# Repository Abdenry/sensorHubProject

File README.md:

# Sensor Hub

A small, portable, self-sustaining weather station built to provide data to an external web interface hosted with Grafana via a Raspberry Pi Zero 2 W. This station is able to collect various metrics from on board sensors such as temperature, humidity, heat index, wind speed, and wind direction. A **DHT22** sensor is used to collect relative humidity and temperature metrics with an accuracy of +-2% and +-0.5C, while metrics such as wind speed and wind direction are collected with custom built sensors. The heat index is calculated in software using the [DHT-sensor-library](https://github.com/adafruit/DHT-sensor-library).

Communication is handled through the NRF24l01 radio modules in a mesh configuration. The mesh routing of data packets is automatically managed with `RF24.h`, `RF24Network.h`, and `RF24Mesh.h` provided by the [RF24](https://github.com/nRF24/RF24?tab=readme-ov-file) library, specifically chosen for its meshing capabilities. It provides dynamic configuration of the NRF24l01 modules, meaning that in the scenario where the weather station loses connection with the Raspberry Pi for any reason (power down, range lost, etc.), it can automatically reconfigure and connect to the Raspberry Pi given its under normal operable condition (i.e. has power and is in range). This allows additional stations to be installed with potentially different purposes with all metrics collected to be routed back to the Raspberry Pi. Alternatively, if the distance between the Raspberry Pi and the weather station is much greater than the range of a single NRF24l01 module, an additional node can be configured and placed in between the weather station and Raspberry Pi acting as a range extender. The RF24 library will automatically handle the routing and pass the data collected from the weather station to the Raspberry Pi via that additional node. There is no limitation that prevents an additional station from also being a range extending node.

### Wiring Diagram

### CAD Model

## Sensor Design
The following sensor assemblies were all 3D printed out of white PET-G filament for its UV resistance, and to reflect as much heat as possible to avoid compromising the temperature and humidity readings of the DHT22 sensor.
### Solar Radiation Shield
The DHT22 sensor used to collect temperature and humidity data was housed in a solar radiation shield. This is necessary to prevent direct sunlight from heating the sensor over time creating higher than ambient temperature readings, simultaneously it protects the sensor from rainfall, which would also cause a higher than ambient humidity reading if it gets wet.

### Wind Vane
Wind direction was measured using eight AH180 omni-polar hall effect sensors and a magnet on the underside of the vane. Each hall effect sensor acts as one of the four cardinal or ordinal directions (North, North East, East, etc.) which is activated only in the presence of the magnet. The vane will point in the direction the wind is blowing **from**. With limited IO available on the Arduino Nano/ATmega328p the SN74HC175N Parallel In Serial Out (PISO) Shift Register was used to reduce the eight outputs of the wind vane to one output + three inputs, halving the total amount of connections to the Arduino Nano/ATmega328p.

### Anemometer
Wind speed was measured using two magnets and a single US1881 latching hall effect sensor connected to the Arduino Nano D2 pin which corresponds to the ATmega328p external interrupt pin 0 (PD2). The magnets attached to the underside of the anemometer rotate over the US1881 sensor triggering either a high or low state depending on the magnets polarity, generating an interrupt which increments a revolution counter. The `getWindSpeed()` function is called periodically to calculate the wind speed using the amount of revolutions counted within that period, resetting the revolution counter once calculation has completed, and repeats this process. This assembly was tested by having the anemometer attached externally to a moving car, logging its calculated wind speed and comparing it to that the vehicles actual speed. It proved accurate to +-2 km/h with a vehicle speed of 80 km/h.

## Grafana Dashboard
The Grafana dashboard conveniently displays historical readings for temperature, humidity, wind speed, and direction. It also provides an updated reading of the stations current temperature, humidity, and calculated heat index. The dashboard has been configured to retain this information for up to two weeks however this can be further increased if desired.

## Power Supply and Challenges Faced
Power for the station comes from a 1100 mAh LiPo battery, supported by four 1W solar panels connected in parallel. A solar power manager with Maximum Power Point Tracking (MPPT) is implemented to maximise the efficiency of the solar panels, switching between charging the station and its battery based on sunlight availability. It ensures that the battery remains charged during daylight hours, with enough capacity to keep the station operational overnight. After optimisations, the weather station consumes approximately 0.021 A at 3.72 V, providing an estimated 52 hours of operation without any solar input.

Prior to optimising power consumption, a major challenge faced during development was the intermittent loss of communications particularly over night.

Initially, it was suspected that the issue was not related to power due to the assumption that the 4 watt solar panel array was capable of powering and charging the station which had a measured active consumption of 0.24W (65mA @ 3.7V). After investigating the issue for a significant period of time, no definitive answer could explain the intermittent communication loss overnight other than insufficient solar power. To prove this was the root of the problem the station was connected to a bench top power supply with a constant 3.7V over night. This resulted in no communication drop outs over night nor for the next couple of days as the battery was sufficiently charged from the constant 3.7 V provided by the power supply. Optimisations for the code then proceeded to lower the active consumption.

### Optimisations
The first optimisation was replacing the software timer used to intermittently send weather metrics to the Raspberry Pi to a Watchdog Timer. This did not directly improve the power consumption of the station, however, it would allow the station to wake up from a power down mode, which was the second optimisation performed.

Entering the Arduino Nano/ATmega328p into a power down mode and only powering up after the Watchdog Timer expired directly reduced power consumption from 0.24W (65mA @ 3.7V) to 0.208W (56mA @ 3.7V), a 13% power efficiency improvement.

This was further improved by 64% by powering down the NRF24l01 radio module when not in use. This lowered the active consumption of the station to just 0.0744W (20mA @ 3.7V). This is a total 69% improvement from the initial 0.24W (65mA @ 3.7V) observed prior to optimising.

With the stations active power consumption optimised, the 4W solar panel array was able to sufficiently charge and power the station eliminating the intermittent communication loss.

## Future Improvements
- This station could be improved in the future with the inclusion of a rainfall sensor to collect metrics on the volume and rate of rainfall. One possible design for this sensor could involve a tipping bucket mechanism, where a known volume of rain causes a bucket to tip, triggering a hall-effect sensor to log the event. By counting the frequency of tipping, the system could accurately measure rate and cumulative rainfall over time.
- Improvements could also be made to the assembly of the custom sensors to be more accessible for servicing as the current design is finicky to put together, not suitable for consistently taking apart and putting back together.
- The internal wiring of the station could also be significantly improved by switching the single core wire used for **each** connection, to a multi-core cable. This could make the internal wiring much tidier and easier to access/service.

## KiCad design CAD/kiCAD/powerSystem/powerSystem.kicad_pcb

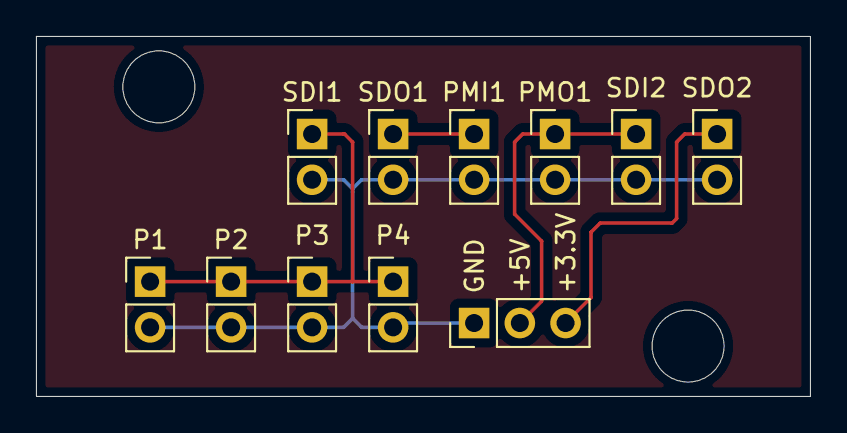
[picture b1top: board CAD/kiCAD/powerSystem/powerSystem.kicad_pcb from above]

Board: 2 copper layers, 43.0 x 20.0 mm, 11 parts (0 on the bottom side), 5 nets.

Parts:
P1, P2, P3, P4: Conn_01x02; PinHeader_1x02_P2.54mm_Vertical
PMI1: Conn_01x02; PinHeader_1x02_P2.54mm_Vertical
PMO1: Conn_01x02; PinHeader_1x02_P2.54mm_Vertical
SDI1, SDI2: Conn_01x02; PinHeader_1x02_P2.54mm_Vertical
SDO1, SDO2: Conn_01x02; PinHeader_1x02_P2.54mm_Vertical
SIGOUT1: Conn_01x03; PinHeader_1x03_P2.54mm_Vertical

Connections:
/0~10V: P1.1, P2.1, P3.1, P4.1, SDI1.1
/+3_3V: SDO2.1, SIGOUT1.3
/+5.5V: PMI1.1, SDO1.1
/+5V: PMO1.1, SDI2.1, SIGOUT1.2
/GND: P1.2, P2.2, P3.2, P4.2, PMI1.2, PMO1.2, SDI1.2, SDI2.2, SDO1.2, SDO2.2, SIGOUT1.1

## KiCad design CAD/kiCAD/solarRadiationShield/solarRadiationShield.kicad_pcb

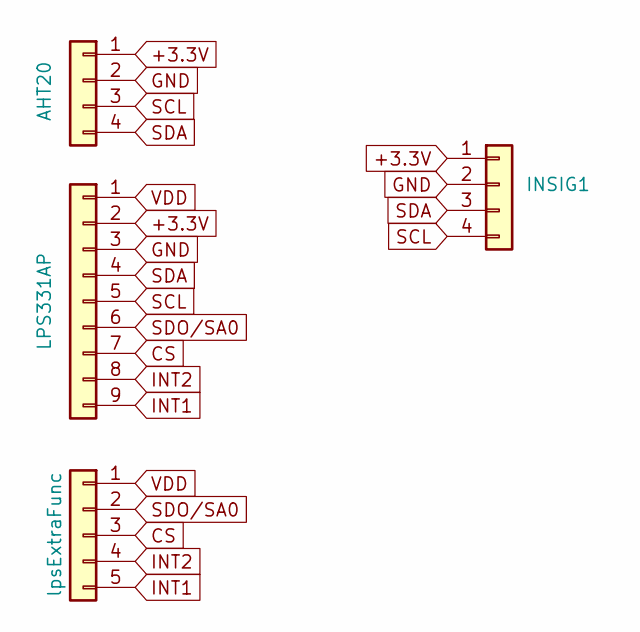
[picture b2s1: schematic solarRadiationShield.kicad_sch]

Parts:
AHT20: AHT20; PinHeader_1x04_P2.54mm_Vertical
INSIG1: INSIG; PinHeader_1x04_P2.54mm_Vertical
LPS331AP1: LPS331AP; PinHeader_1x09_P2.54mm_Vertical
lpsExtraFunc1: lpsExtraFunc; PinHeader_1x05_P2.54mm_Vertical

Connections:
+3.3V: AHT20.1, INSIG1.1, LPS331AP1.2
CS: LPS331AP1.7, lpsExtraFunc1.3
GND: AHT20.2, INSIG1.2, LPS331AP1.3
INT1: LPS331AP1.9, lpsExtraFunc1.5
INT2: LPS331AP1.8, lpsExtraFunc1.4
SCL: AHT20.3, INSIG1.4, LPS331AP1.5
SDA: AHT20.4, INSIG1.3, LPS331AP1.4
SDO/SA0: LPS331AP1.6, lpsExtraFunc1.2
VDD: LPS331AP1.1, lpsExtraFunc1.1

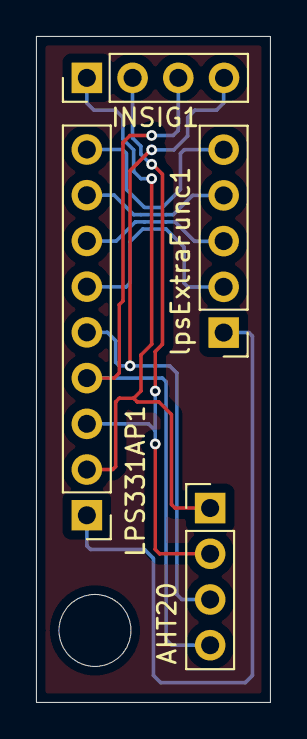
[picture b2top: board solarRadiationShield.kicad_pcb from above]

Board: 2 copper layers, 13.0 x 37.0 mm, 4 parts (0 on the bottom side), 9 nets.

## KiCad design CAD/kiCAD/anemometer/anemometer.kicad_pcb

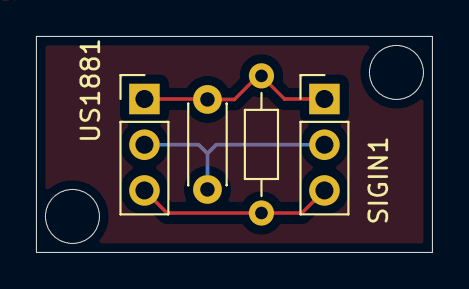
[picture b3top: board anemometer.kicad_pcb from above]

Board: 2 copper layers, 22.0 x 12.0 mm, 4 parts (0 on the bottom side), 3 nets.

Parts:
C1: 100nF; C_Disc_D4.3mm_W1.9mm_P5.00mm
R1: 10k; R_Axial_DIN0204_L3.6mm_D1.6mm_P7.62mm_Horizontal
SIGIN1: Conn_01x03; PinHeader_1x03_P2.54mm_Vertical
US1881: Conn_01x03; PinHeader_1x03_P2.54mm_Vertical

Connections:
GND: C1.1, SIGIN1.2, US1881.2
OUT: R1.2, SIGIN1.3, US1881.3
VDD: C1.2, R1.1, SIGIN1.1, US1881.1

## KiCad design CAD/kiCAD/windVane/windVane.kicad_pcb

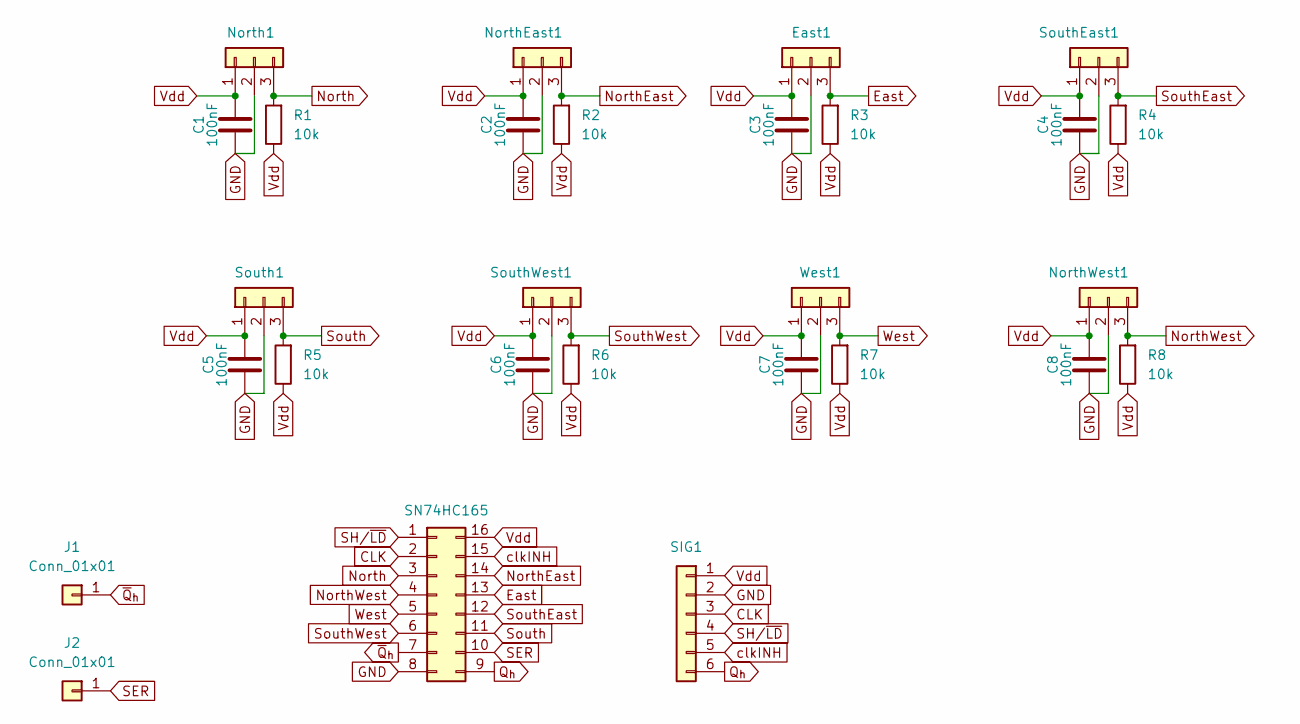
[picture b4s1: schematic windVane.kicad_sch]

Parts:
C1, C2, C3, C4, C5, C6, C7, C8: 100nF; C_0402_1005Metric
East1: Conn_01x03; PinHeader_1x03_P2.54mm_Vertical
J1, J2: Conn_01x01; PinHeader_1x01_P2.54mm_Vertical
North1: Conn_01x03; PinHeader_1x03_P2.54mm_Vertical
NorthEast1: Conn_01x03; PinHeader_1x03_P2.54mm_Vertical
NorthWest1: Conn_01x03; PinHeader_1x03_P2.54mm_Vertical
R1, R2, R3, R4, R5, R6, R7, R8: 10k; R_0402_1005Metric
SIG1: Conn_01x06; PinHeader_1x06_P2.54mm_Vertical
SN74HC165: Conn_02x08_Counter_Clockwise; DIP-16_W7.62mm
South1: Conn_01x03; PinHeader_1x03_P2.54mm_Vertical
SouthEast1: Conn_01x03; PinHeader_1x03_P2.54mm_Vertical
SouthWest1: Conn_01x03; PinHeader_1x03_P2.54mm_Vertical
West1: Conn_01x03; PinHeader_1x03_P2.54mm_Vertical

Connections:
CLK: SIG1.3, SN74HC165.2
East: East1.3, R3.2, SN74HC165.13
GND: C1.1, C2.1, C3.1, C4.1, C5.1, C6.1, C7.1, C8.1, East1.2, North1.2, NorthEast1.2, NorthWest1.2, SIG1.2, SN74HC165.8, South1.2, SouthEast1.2, SouthWest1.2, West1.2
North: North1.3, R1.2, SN74HC165.3
NorthEast: NorthEast1.3, R2.2, SN74HC165.14
NorthWest: NorthWest1.3, R8.2, SN74HC165.4
Q_{h}: SIG1.6, SN74HC165.9
SER: J2.1, SN74HC165.10
SH/~LD: SIG1.4, SN74HC165.1
South: R5.2, SN74HC165.11, South1.3
SouthEast: R4.2, SN74HC165.12, SouthEast1.3
SouthWest: R6.2, SN74HC165.6, SouthWest1.3
Vdd: C1.2, C2.2, C3.2, C4.2, C5.2, C6.2, C7.2, C8.2, East1.1, North1.1, NorthEast1.1, NorthWest1.1, R1.1, R2.1, R3.1, R4.1, R5.1, R6.1, R7.1, R8.1, SIG1.1, SN74HC165.16, South1.1, SouthEast1.1, SouthWest1.1, West1.1
West: R7.2, SN74HC165.5, West1.3
clkINH: SIG1.5, SN74HC165.15
~Q_{h}: J1.1, SN74HC165.7

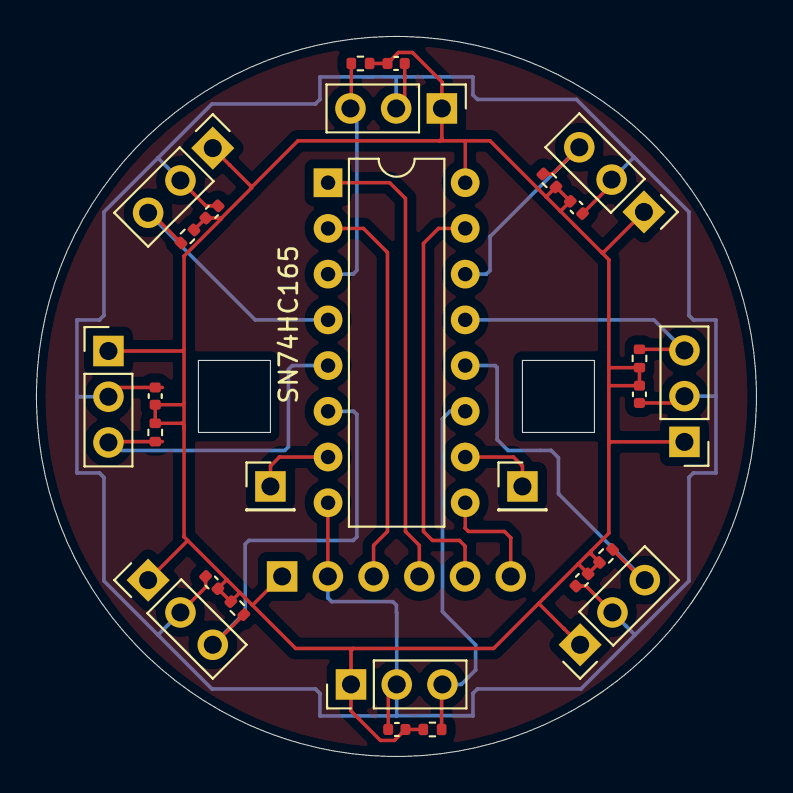
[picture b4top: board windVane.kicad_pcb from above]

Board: 2 copper layers, 40.0 x 40.0 mm, 28 parts (1 on the bottom side), 16 nets.

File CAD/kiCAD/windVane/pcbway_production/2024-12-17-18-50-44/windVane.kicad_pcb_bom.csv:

Designator,Quantity,Value,Footprint,Package,MPN,DNP,Mount_Type,Description
"C1, C2, C3, C4, C5, C6, C7, C8",8,100nF,C_0402_1005Metric,,,,smt,Unpolarized capacitor
"East1, North1, NorthEast1, NorthWest1, South1, SouthEast1, SouthWest1, West1",8,Conn_01x03,PinHeader_1x03_P2.54mm_Vertical,,,,tht,"Generic connector, single row, 01x03, script generated (kicad-library-utils/schlib/autogen/connector/)"
"J1, J2",2,Conn_01x01,PinHeader_1x01_P2.54mm_Vertical,,,,tht,"Generic connector, single row, 01x01, script generated (kicad-library-utils/schlib/autogen/connector/)"
"R1, R2, R3, R4, R5, R6, R7, R8",8,10k,R_0402_1005Metric,,,,smt,Resistor
SIG1,1,Conn_01x06,PinHeader_1x06_P2.54mm_Vertical,,,,tht,"Generic connector, single row, 01x06, script generated (kicad-library-utils/schlib/autogen/connector/)"
SN74HC165,1,Conn_02x08_Counter_Clockwise,DIP-16_W7.62mm,,,,tht,"Generic connector, double row, 02x08, counter clockwise pin numbering scheme (similar to DIP package numbering), script generated (kicad-library-utils/schlib/autogen/connector/)"

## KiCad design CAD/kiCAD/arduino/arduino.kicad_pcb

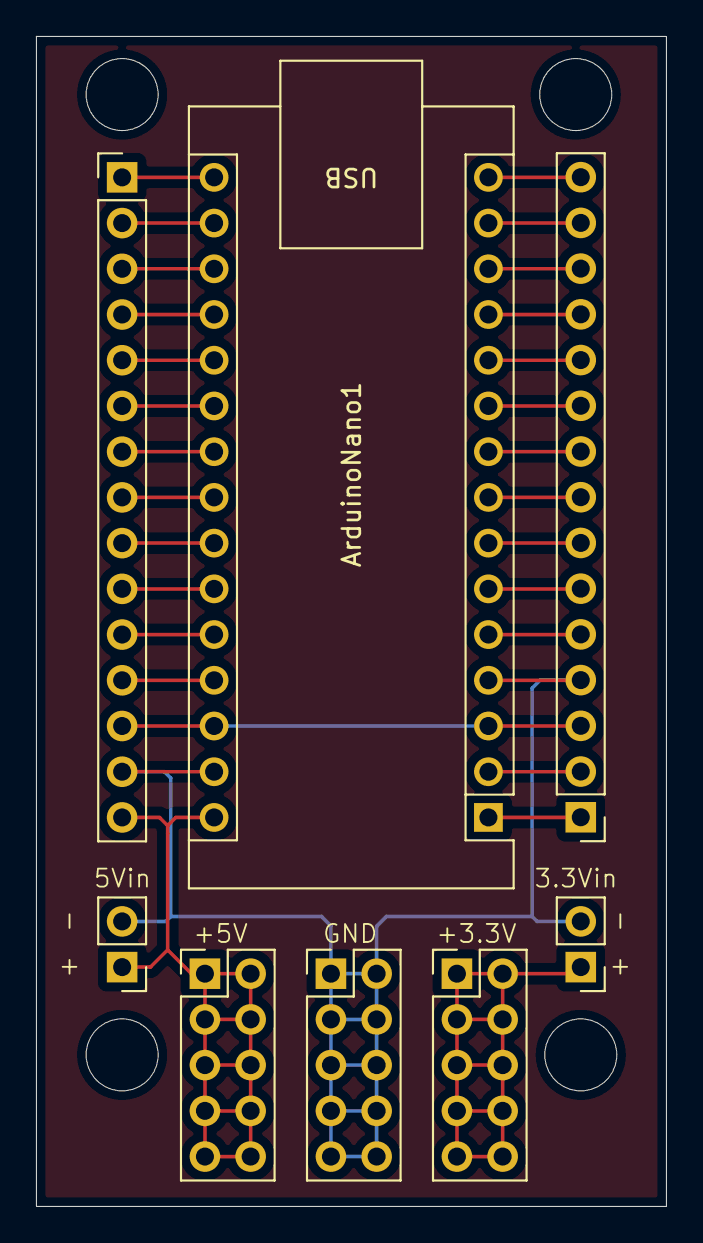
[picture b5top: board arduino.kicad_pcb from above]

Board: 2 copper layers, 35.0 x 65.0 mm, 8 parts (0 on the bottom side), 29 nets.

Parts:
3.3Vbar1, 5Vbar1: Conn_02x05_Counter_Clockwise; PinHeader_2x05_P2.54mm_Vertical
5Vin1: Conn_01x02; PinHeader_1x02_P2.54mm_Vertical
ArduinoNano1: Arduino_Nano_v3.x; Arduino_Nano
Expansion1, Expansion2: Conn_01x15; PinHeader_1x15_P2.54mm_Vertical
GNDBar1: Conn_02x05_Counter_Clockwise; PinHeader_2x05_P2.54mm_Vertical
powerIN2: Conn_01x02; PinHeader_1x02_P2.54mm_Vertical

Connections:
+3.3V: 3.3Vbar1.1, 3.3Vbar1.2, 3.3Vbar1.3, 3.3Vbar1.4, 3.3Vbar1.5, 3.3Vbar1.6, 3.3Vbar1.7, 3.3Vbar1.8, 3.3Vbar1.9, 3.3Vbar1.10, powerIN2.1
+5V: 5Vbar1.1, 5Vbar1.2, 5Vbar1.3, 5Vbar1.4, 5Vbar1.5, 5Vbar1.6, 5Vbar1.7, 5Vbar1.8, 5Vbar1.9, 5Vbar1.10, 5Vin1.1, ArduinoNano1.30 (VIN), Expansion2.15
A0: ArduinoNano1.19 (A0), Expansion2.4
A1: ArduinoNano1.20 (A1), Expansion2.5
A2: ArduinoNano1.21 (A2), Expansion2.6
A3: ArduinoNano1.22 (A3), Expansion2.7
A4: ArduinoNano1.23 (A4), Expansion2.8
A5: ArduinoNano1.24 (A5), Expansion2.9
A6: ArduinoNano1.25 (A6), Expansion2.10
A7: ArduinoNano1.26 (A7), Expansion2.11
AREF: ArduinoNano1.18 (AREF), Expansion2.3
D0: ArduinoNano1.2 (D0/RX), Expansion1.2
D1: ArduinoNano1.1 (D1/TX), Expansion1.1
D2: ArduinoNano1.5 (D2), Expansion1.5
D3: ArduinoNano1.6 (D3), Expansion1.6
D4: ArduinoNano1.7 (D4), Expansion1.7
D5: ArduinoNano1.8 (D5), Expansion1.8
D6: ArduinoNano1.9 (D6), Expansion1.9
D7: ArduinoNano1.10 (D7), Expansion1.10
D8: ArduinoNano1.11 (D8), Expansion1.11
D9: ArduinoNano1.12 (D9), Expansion1.12
D10: ArduinoNano1.13 (D10), Expansion1.13
D11: ArduinoNano1.14 (D11), Expansion1.14
D12: ArduinoNano1.15 (D12), Expansion1.15
D13: ArduinoNano1.16 (D13), Expansion2.1
GND: 5Vin1.2, ArduinoNano1.4 (GND), ArduinoNano1.29 (GND), Expansion1.4, Expansion2.14, GNDBar1.1, GNDBar1.2, GNDBar1.3, GNDBar1.4, GNDBar1.5, GNDBar1.6, GNDBar1.7, GNDBar1.8, GNDBar1.9, GNDBar1.10, powerIN2.2
RST: ArduinoNano1.3 (~RESET), ArduinoNano1.28 (~RESET), Expansion1.3, Expansion2.13
nano3.3V: ArduinoNano1.17 (3V3), Expansion2.2
nano5V: ArduinoNano1.27 (+5V), Expansion2.12

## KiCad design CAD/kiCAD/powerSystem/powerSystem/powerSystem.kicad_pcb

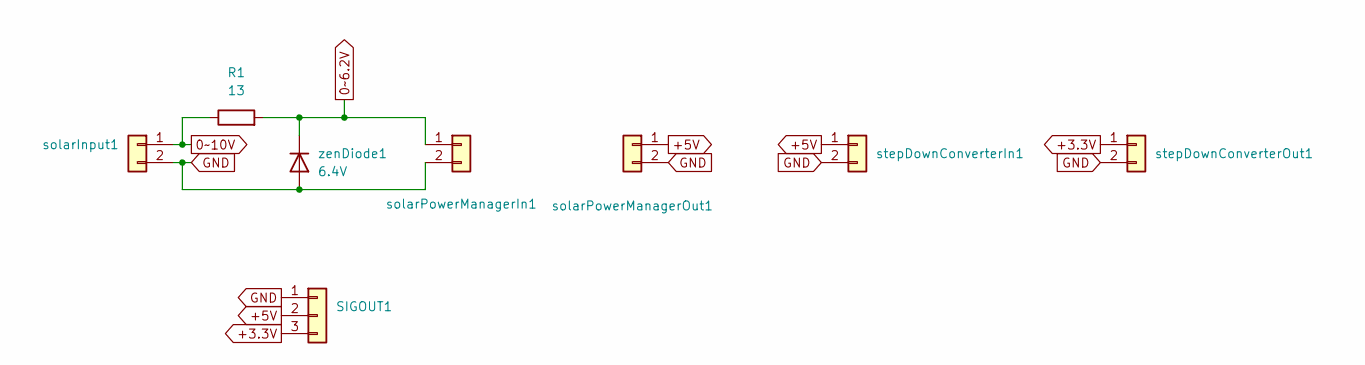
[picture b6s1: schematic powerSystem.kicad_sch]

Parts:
R1: 13; R_Axial_DIN0204_L3.6mm_D1.6mm_P7.62mm_Horizontal
SIGOUT1: Conn_01x03; PinHeader_1x03_P2.54mm_Vertical
solarInput1: Conn_01x02; PinHeader_1x02_P2.54mm_Vertical
solarPowerManagerIn1: Conn_01x02; PinHeader_1x02_P2.54mm_Vertical
solarPowerManagerOut1: Conn_01x02; PinHeader_1x02_P2.54mm_Vertical
stepDownConverterIn1: Conn_01x02; PinHeader_1x02_P2.54mm_Vertical
stepDownConverterOut1: Conn_01x02; PinHeader_1x02_P2.54mm_Vertical
zenDiode1: 6.4V; D_DO-41_SOD81_P7.62mm_Horizontal

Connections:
0~6.2V: R1.2, solarPowerManagerIn1.1, zenDiode1.1 (K)
0~10V: R1.1, solarInput1.1
+3.3V: SIGOUT1.3, stepDownConverterOut1.1
+5V: SIGOUT1.2, solarPowerManagerOut1.1, stepDownConverterIn1.1
GND: SIGOUT1.1, solarInput1.2, solarPowerManagerIn1.2, solarPowerManagerOut1.2, stepDownConverterIn1.2, stepDownConverterOut1.2, zenDiode1.2 (A)

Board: 2 copper layers, 8 parts (0 on the bottom side), 5 nets, no tracks yet.

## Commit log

2024-09-23 Added Files
2024-10-01 Organized
2024-10-11 Updated BOM
2024-10-11 Weather Station Notes
2024-10-12 Updated parts to be used
2024-10-14 Added magnet cost
2024-10-14 Updated BOM materials
2024-10-14 Spelling errors
2024-10-21 Include and Define
2024-10-21 Update Main.cpp
    Moved include files to main.h and modified code to read data from AHT20, and LPS331AP.
    Currenly can only read one sensor at a time and data casted to UINT32 as master node has not been configured for multiple inputs and float data.
2024-10-21 AHT20 library
2024-10-21 LPS331AP Library
2024-10-22 Raspberry Pi branch for MAKEFILE testing.
2024-10-23 Modifed main.cpp and created Makefile main.cpp now should now work with raspberry pi zero 2 w if the rf24libs have been installed correctly to ~/rf24libs (default). Ensure the rf24 installation scrip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
2024-10-23 Altered main to read data sent from all sensors.
2024-10-23 Updated sensor to send packet data
2024-10-23 Added Arduino Nano to BOM
2024-11-10 Updated ignorefiles
2024-11-10 POST sensor data
2024-11-12 [Time updates]
2024-11-14 Updated performance on RPI
2024-11-20 CAD UPDATES
2024-11-20 Updated mBar to Bar
2024-11-21 kiCAD files
2024-11-22 Electrical Schematic Updates
2024-11-25 Update Schematics
2024-11-26 Updated Circuit Diagram
2024-11-27 Cross checked schematic with diagram layout
2024-11-27 Created power system schematic
2024-11-27 changed file name
2024-12-03 Big Updates
2025-02-10 Big Updates Good Luck
2025-02-10 Temp fix of hanging sensor
    - Enabled Timeouts in twi.c and Wire_timeout.h
    - Temp error checking handled in main.cpp
    Ideally break the main loop into individual function calls so that if a sensor is lost it can just be ignored.
2025-02-11 Created sendPacket(); fixed windspeed delay
    Created sendPacket() function that accepts a generic structure and sends it via RF.
    Used to send different data packets with same function call.
    Wrapped "aht20.getMeasurement()" with initAHT20 as it would delay the ISR when AHT20 in a non functioning state otherwise.
2025-02-12 Incomplete
2025-02-12 Added getWindSpeed function
    Simple function that stores the windspeed calculated directly into data packet.windSpeed.
    Commented out getAHT20Data as it causes issues with sending data.
2025-02-12 fixed getAHT20Data; code tidy
2025-02-12 Updated Master Node main.cpp
2025-02-12 Created lsp331AP function
2025-02-13 Updated sendPacket and getWindSpeed
    - Changed sendPacket to accept a sensorData_t type for debugging purpose.
    - getWindSpeed can now directly alter the values of the struct similar to other functions.
2025-02-13 Updated main.cpp
    - Add float limits to print statement
    - Changed the declaration of structure to match C format
2025-02-14 Added sensor verifcation method before posting data to webserver
2025-02-14 Changed console output format
2025-02-14 Post no data if CURL failed
2025-02-14 Added sensor verification methods to packet data
2025-02-23 Code Refactor; Removed Blocking Time Interval
    - Dedicated setup functions for different parts of the system.
    - Software timer now used to send a packet X seconds rather than a blocking time difference check. Done to mitigate chances of blocking code interfering with interrupts.
2025-03-06 Updated sensor code
    Removed LPS, AHT20 sensors
    Added DHT22 sensor
2025-03-06 Updated for 4 solar panels
2025-03-06 Added DHT22, removed AHT20/LPS
2025-03-06 removed AHT20/LPS sensor; added AHT22 sensor
2025-03-07 Added wind direction
2025-03-07 Fixed Structure Order
2025-03-07 Fixed Struct Order
2025-04-12 Switched software timer to WDT, optimized power consumption from 64 mA @ 3.7V to 21 mA @ 3.7V
2025-04-12 Adjusted terminal output layout, added time stamp to output log
